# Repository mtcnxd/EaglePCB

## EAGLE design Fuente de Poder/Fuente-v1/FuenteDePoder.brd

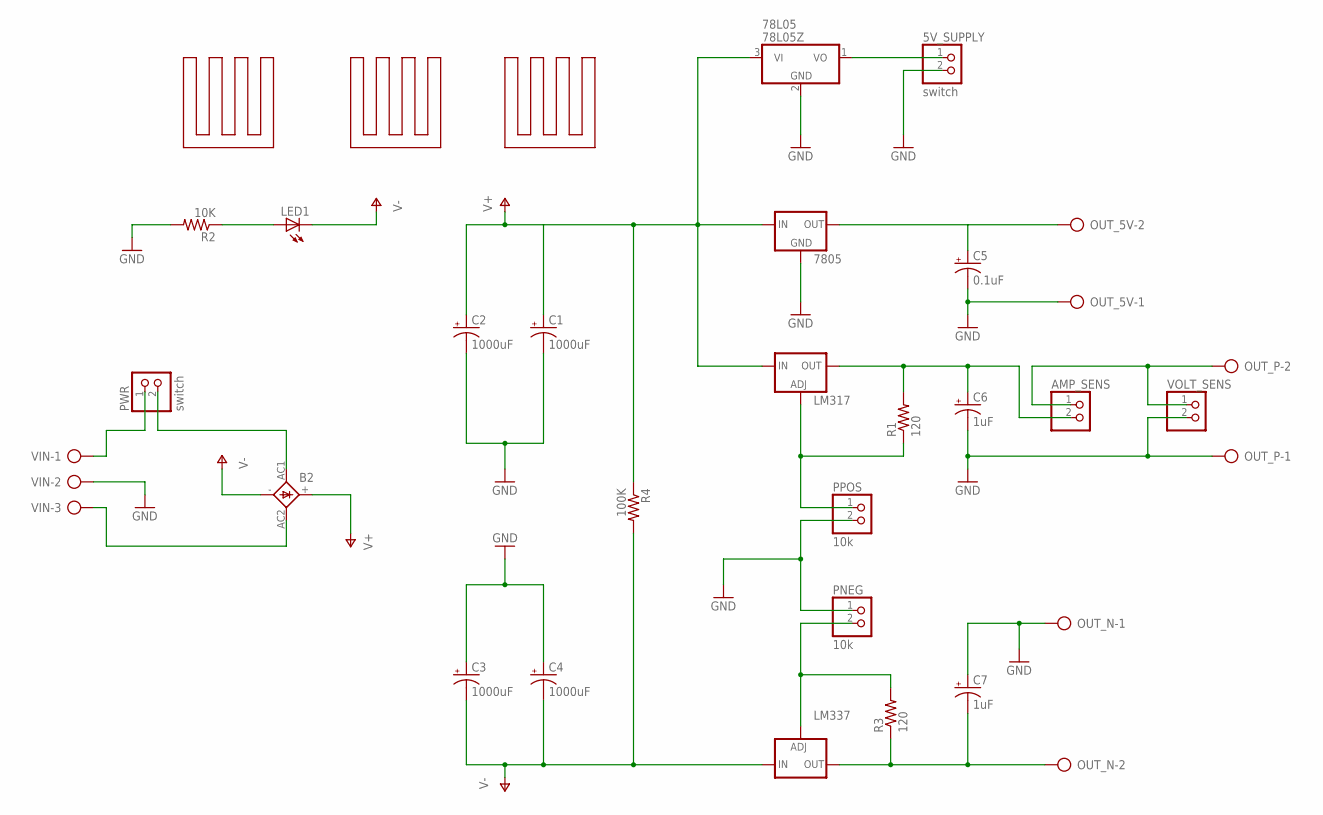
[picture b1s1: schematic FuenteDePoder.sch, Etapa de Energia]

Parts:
5V_SUPPLY: switch; 1X02
78L05: 78L05Z; TO92
7805: 78XXS
AMP_SENS: PINHD-1X2; 1X02
B2: GBPC6
C1, C2, C3, C4: 1000uF; E3,5-10
C5: 0.1uF; E1,8-4
C6, C7: 1uF; E1,8-4
LED1: LED5MM
LM317: LM317TS; 317TS
LM337: LM337TS; 337TS
OUT_5V: AK300/2
OUT_N: AK300/2
OUT_P: AK300/2
PNEG: 10k; 1X02
PPOS: 10k; 1X02
PWR: switch; 1X02
R1, R3: 120; 0204/7
R2: 10K; 0204/7
R4: 100K; 0204/7
U$1, U$2, U$3: HEATSINK
VIN: AK300/3
VOLT_SENS: PINHD-1X2; 1X02

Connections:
GND: 5V_SUPPLY.2, 78L05.2 (GND), 7805.GND, C1.-, C2.-, C3.+, C4.+, C5.-, C6.-, C7.+, OUT_5V.1, OUT_N.1, OUT_P.1, PNEG.1, PPOS.2, R2.2, VIN.2, VOLT_SENS.2
unnamed: B2.AC1, PWR.2
unnamed: B2.AC2, VIN.3
unnamed: LED1.A, R2.1
unnamed: C7.-, LM337.3 (OUT), OUT_N.2, R3.1
unnamed: 5V_SUPPLY.1, 78L05.1 (VO)
unnamed: LM337.1 (ADJ), PNEG.2, R3.2
unnamed: LM317.1 (ADJ), PPOS.1, R1.1
unnamed: PWR.1, VIN.1
unnamed: AMP_SENS.1, OUT_P.2, VOLT_SENS.1
V5: 7805.OUT, C5.+, OUT_5V.2
V12: AMP_SENS.2, C6.+, LM317.2 (OUT), R1.2
V+: 78L05.3 (VI), 7805.IN, B2.+, C1.+, C2.+, LM317.3 (IN), R4.1
V-: B2.-, C3.-, C4.-, LED1.K (C), LM337.2 (IN), R4.2

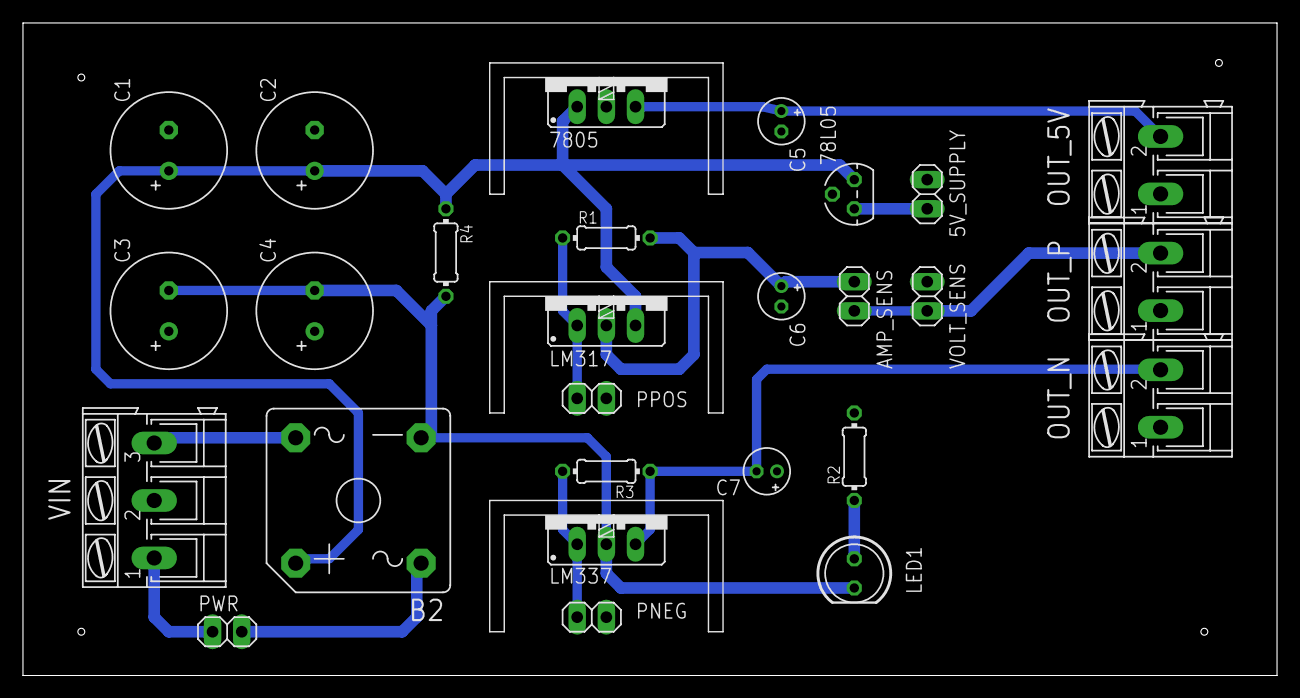
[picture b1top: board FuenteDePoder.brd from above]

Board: 2 copper layers, 109.2 x 56.8 mm, 30 parts (0 on the bottom side), 14 nets.

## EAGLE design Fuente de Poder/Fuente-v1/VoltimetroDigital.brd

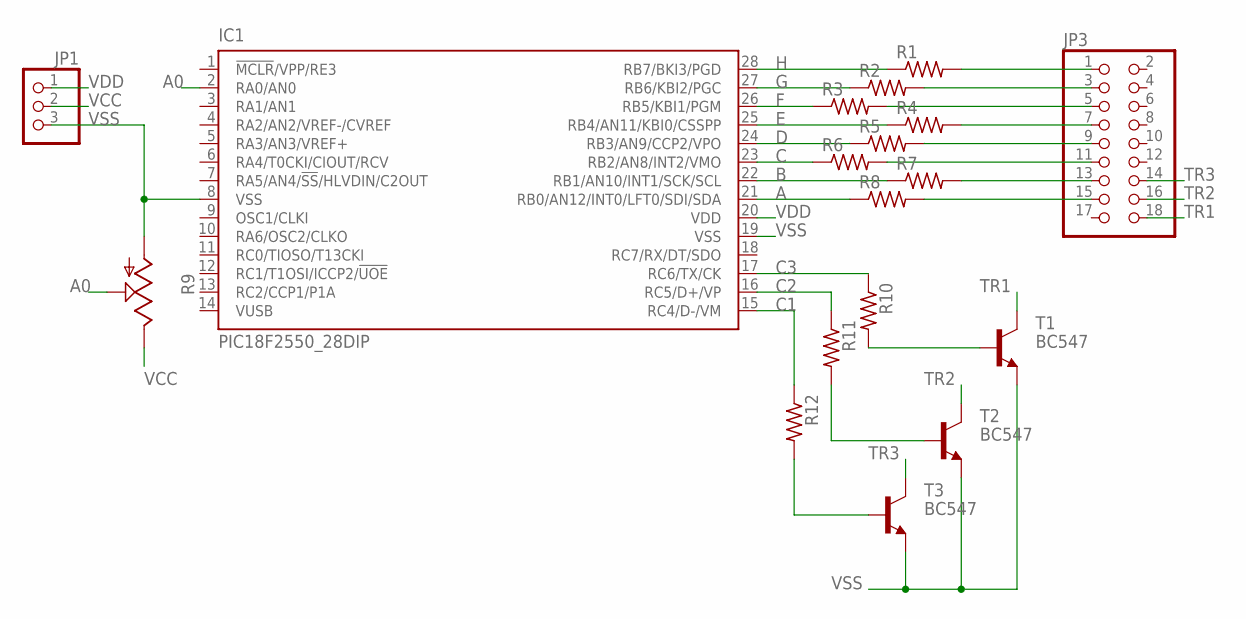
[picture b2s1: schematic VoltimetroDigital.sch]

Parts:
IC1: PIC18F2550_28DIP; DIL28-3
JP1: PINHD-1X3; 1X03
JP3: PINHD-2X9; 2X09
R1, R2, R3, R4, R5, R6, R7, R8, R10, R11, R12: R-US_0204/7; 0204/7
R9: TRIM_US-LI10; LI10
T1, T2, T3: BC547; TO92

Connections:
A: IC1.21 (RB0/AN12/INT0/LFT0/SDI/SDA), R8.1
A0: IC1.2 (RA0/AN0), R9.S
B: IC1.22 (RB1/AN10/INT1/SCK/SCL), R7.1
C: IC1.23 (RB2/AN8/INT2/VMO), R6.1
C1: IC1.15 (RC4/D-/VM), R12.1
C2: IC1.16 (RC5/D+/VP), R11.1
C3: IC1.17 (RC6/TX/CK), R10.1
D: IC1.24 (RB3/AN9/CCP2/VPO), R5.1
E: IC1.25 (RB4/AN11/KBI0/CSSPP), R4.1
F: IC1.26 (RB5/KBI1/PGM), R3.1
G: IC1.27 (RB6/KBI2/PGC), R2.1
H: IC1.28 (RB7/BKI3/PGD), R1.1
unnamed: JP3.1, R1.2
unnamed: JP3.3, R2.2
unnamed: JP3.5, R3.2
unnamed: JP3.7, R4.2
unnamed: JP3.9, R5.2
unnamed: JP3.11, R6.2
unnamed: JP3.13, R7.2
unnamed: JP3.15, R8.2
unnamed: R12.2, T3.2 (B)
unnamed: R11.2, T2.2 (B)
unnamed: R10.2, T1.2 (B)
TR1: JP3.18, T1.3 (C)
TR2: JP3.16, T2.3 (C)
TR3: JP3.14, T3.3 (C)
VCC: JP1.2, R9.E
VDD: IC1.20 (VDD), JP1.1
VSS: IC1.8 (VSS), IC1.19 (VSS), JP1.3, R9.A, T1.1 (E), T2.1 (E), T3.1 (E)

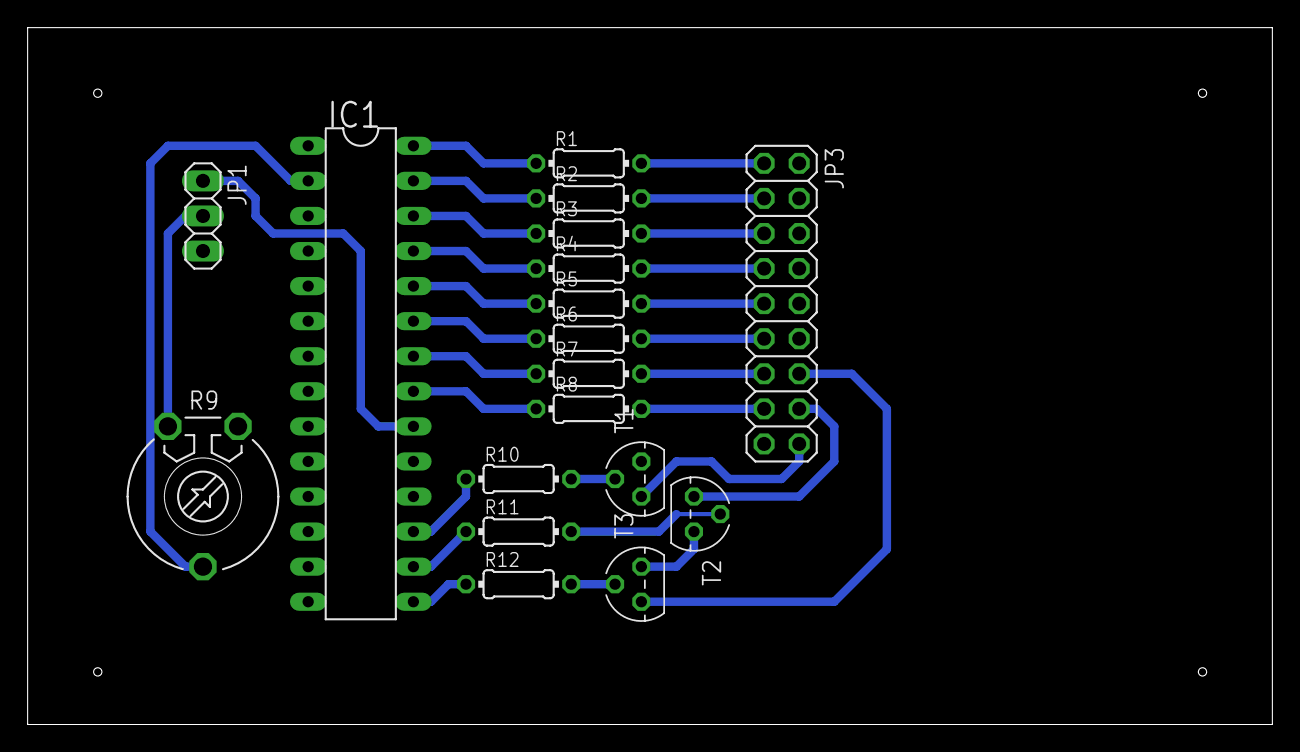
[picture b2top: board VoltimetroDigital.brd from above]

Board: 2 copper layers, 90.2 x 50.5 mm, 18 parts (0 on the bottom side), 29 nets.

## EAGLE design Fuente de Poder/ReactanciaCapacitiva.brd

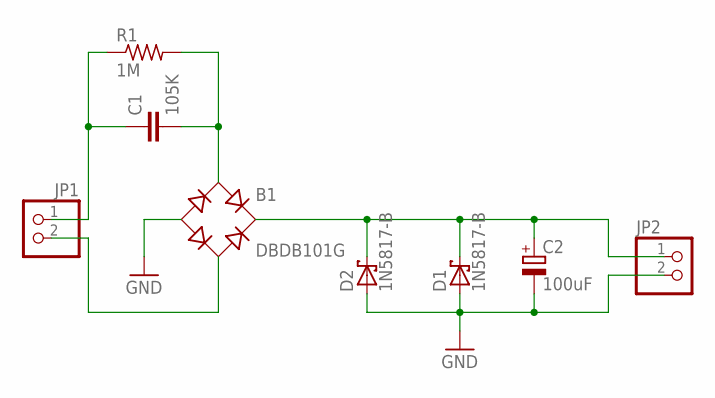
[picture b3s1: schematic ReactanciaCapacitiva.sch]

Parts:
B1: DBDB101G; DB
C1: 105K; C15B7
C2: 100uF; E2,5-7
D1, D2: 1N5817-B; DO41-7.6
JP1: PINHD-1X2/90; 1X02/90
JP2: PINHD-1X2; 1X02
R1: 1M; 0204/7

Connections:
GND: B1.-, C2.-, D1.A, D2.A, JP2.2
unnamed: C1.1, JP1.1, R1.1
unnamed: B1.AC2, JP1.2
unnamed: B1.AC1, C1.2, R1.2
unnamed: B1.+, C2.+, D1.C, D2.C, JP2.1

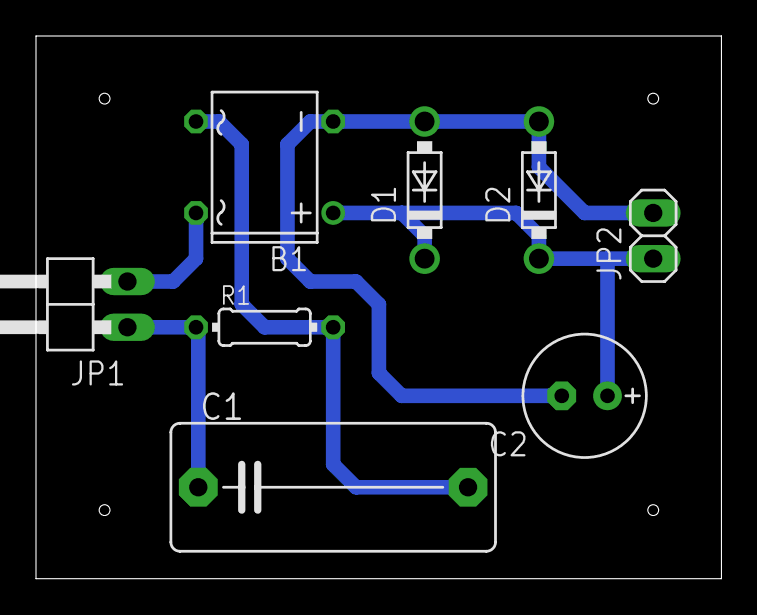
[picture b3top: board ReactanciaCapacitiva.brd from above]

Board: 2 copper layers, 38.1 x 30.1 mm, 8 parts (0 on the bottom side), 5 nets.

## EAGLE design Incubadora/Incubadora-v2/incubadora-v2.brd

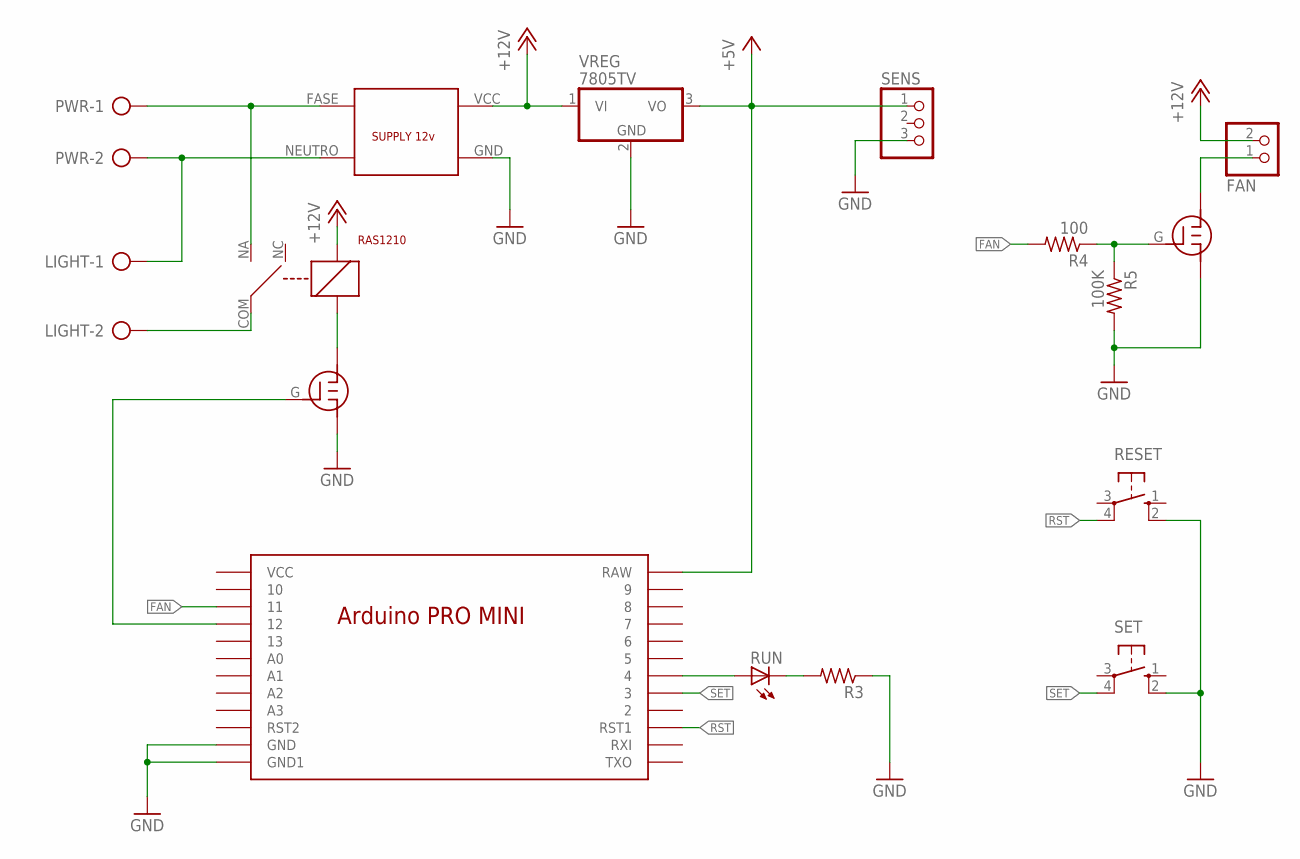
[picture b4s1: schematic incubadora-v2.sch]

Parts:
FAN: PINHD-1X2/90; 1X02/90
LIGHT: AK300/2
PWR: AK300/2
R3: R-US_0204/7; 0204/7
R4: 100; 0204/7
R5: 100K; 0204/7
RAS1210: RAS0510
RESET: 10-XX; B3F-10XX
RUN: LED5MM
SENS: PINHD-1X3/90; 1X03/90
SET: 10-XX; B3F-10XX
U$1: PROMINI
U$2, U$4: J111
U$3: SUPPLY12V
VREG: 7805TV; TO220V

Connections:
+5V: SENS.1, U$1.RAW, VREG.3 (VO)
+12V: FAN.2, RAS1210.B1, U$3.VCC, VREG.1 (VI)
BULB: U$1.12, U$4.G
FAN: R4.2, U$1.11
FASE: PWR.1, RAS1210.NA, U$3.FASE
GND: R3.1, R5.2, RESET.2 (S1), SENS.3, SET.2 (S1), U$1.GND1 (GND), U$1.GND2 (GND1), U$2.S, U$3.GND, U$4.S, VREG.2 (GND)
unnamed: RUN.A, U$1.4
unnamed: LIGHT.2, RAS1210.COM
unnamed: RAS1210.B2, U$4.D
unnamed: R3.2, RUN.K (C)
unnamed: LIGHT.1, PWR.2, U$3.NEUTRO
unnamed: R4.1, R5.1, U$2.G
unnamed: FAN.1, U$2.D
RST: RESET.4 (P1), U$1.RST1
SET: SET.4 (P1), U$1.3

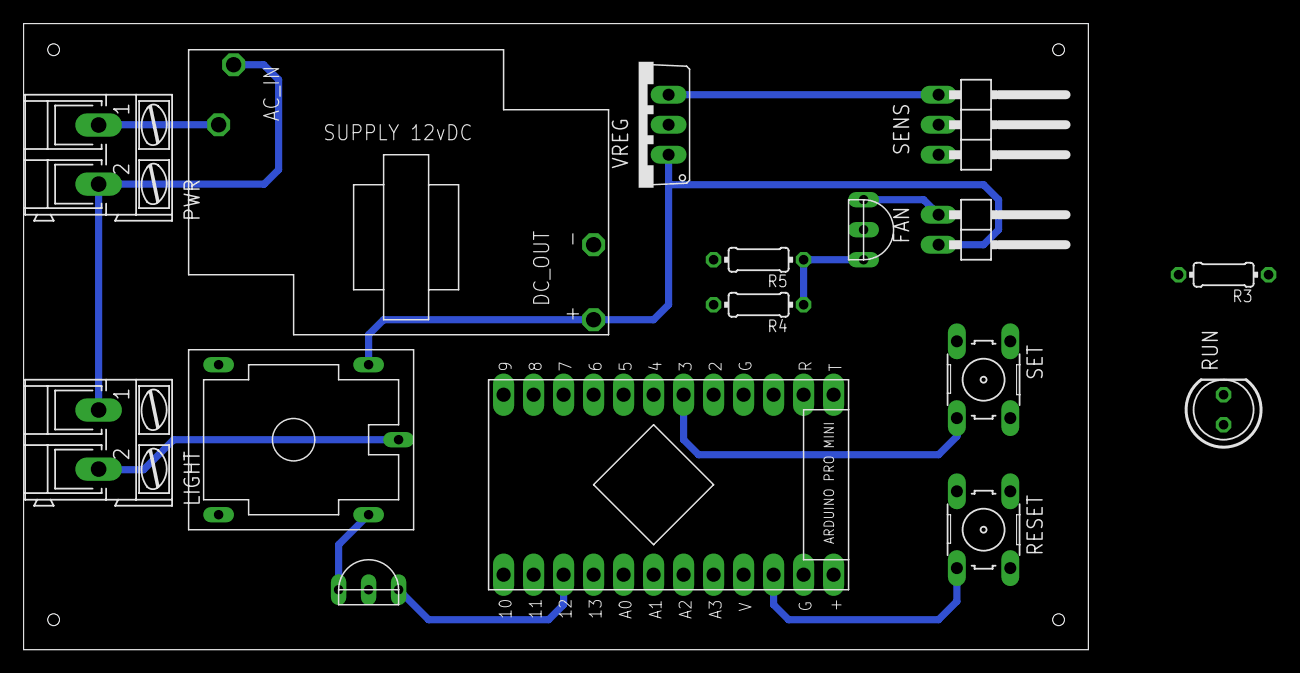
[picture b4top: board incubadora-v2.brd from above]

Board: 2 copper layers, 90.2 x 53.0 mm, 16 parts (0 on the bottom side), 15 nets.

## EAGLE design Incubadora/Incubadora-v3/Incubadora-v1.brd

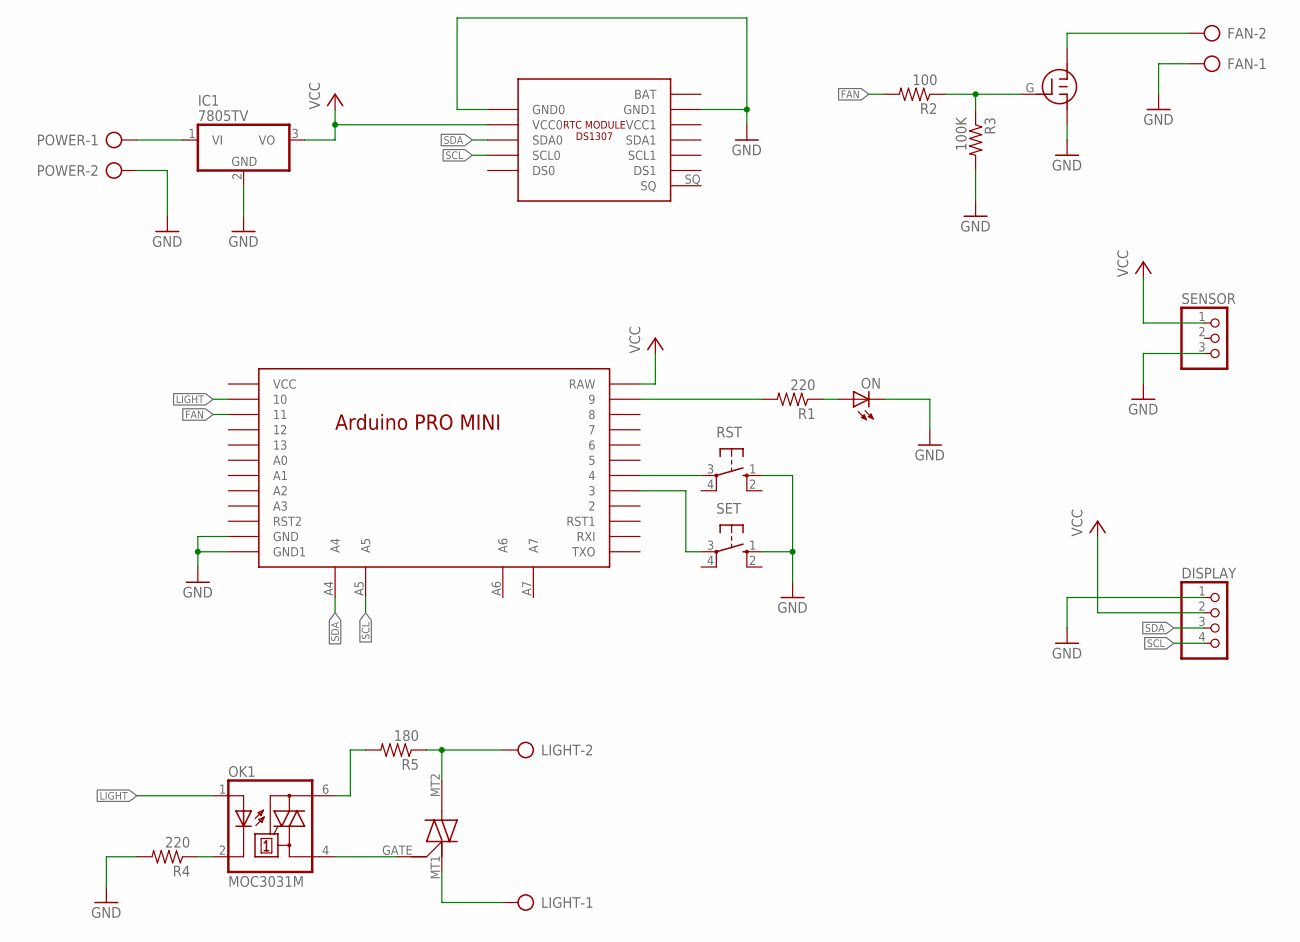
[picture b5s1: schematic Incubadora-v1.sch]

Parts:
DISPLAY: PINHD-1X4; 1X04
FAN: AK300/2
IC1: 7805TV; TO220V
LIGHT: AK300/2
MAC12: MAC12
OK1: MOC3031M; DIL06
ON: LED3MM
POWER: AK300/2
R1, R4: 220; 0204/7
R2: 100; 0204/7
R3: 100K; 0204/7
R5: 180; 0204/7
RST: 10-XX; B3F-10XX
SENSOR: PINHD-1X3/90; 1X03/90
SET: 10-XX; B3F-10XX
U$1: CLOCK
U$2: PROMINI
U$3: J111

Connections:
FAN: R2.2, U$2.11
GND: DISPLAY.1, FAN.1, IC1.2 (GND), ON.K (C), POWER.2, R3.2, R4.2, RST.1 (S), SENSOR.3, SET.1 (S), U$1.GND0, U$1.GND1, U$2.GND1 (GND), U$2.GND2 (GND1), U$3.S
LIGHT: OK1.1 (A), U$2.10
unnamed: ON.A, R1.1
unnamed: IC1.1 (VI), POWER.1
unnamed: RST.3, U$2.4
unnamed: SET.3, U$2.3
unnamed: R1.2, U$2.9
unnamed: FAN.2, U$3.D
unnamed: R2.1, R3.1, U$3.G
unnamed: LIGHT.2, MAC12.MT2, R5.1
unnamed: LIGHT.1, MAC12.MT1
unnamed: OK1.2 (C), R4.1
unnamed: MAC12.GATE, OK1.4 (A1)
unnamed: OK1.6 (A2), R5.2
SCL: DISPLAY.4, U$1.SCL0, U$2.A5
SDA: DISPLAY.3, U$1.SDA0, U$2.A4
VCC: DISPLAY.2, IC1.3 (VO), SENSOR.1, U$1.VCC0, U$2.RAW

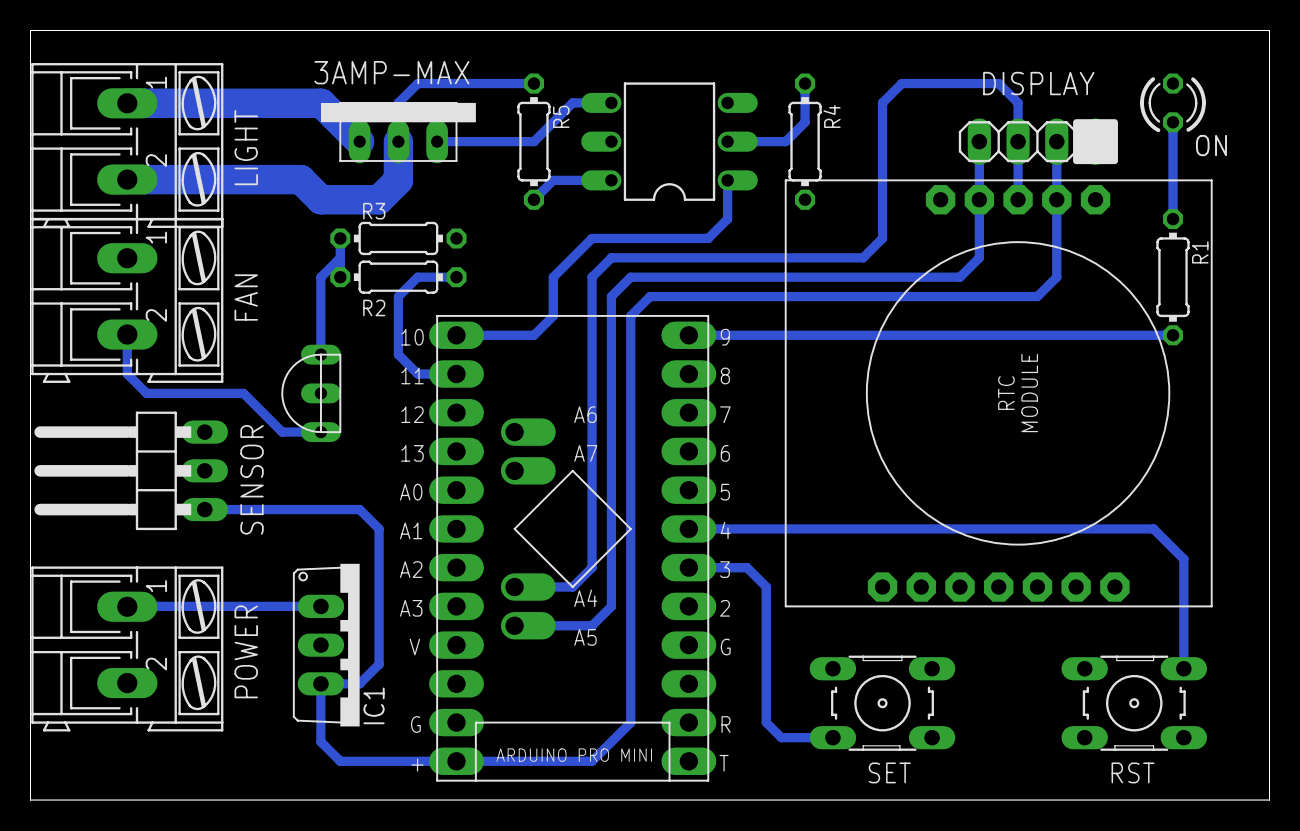
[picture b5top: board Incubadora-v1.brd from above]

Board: 2 copper layers, 81.3 x 50.5 mm, 19 parts (0 on the bottom side), 18 nets.

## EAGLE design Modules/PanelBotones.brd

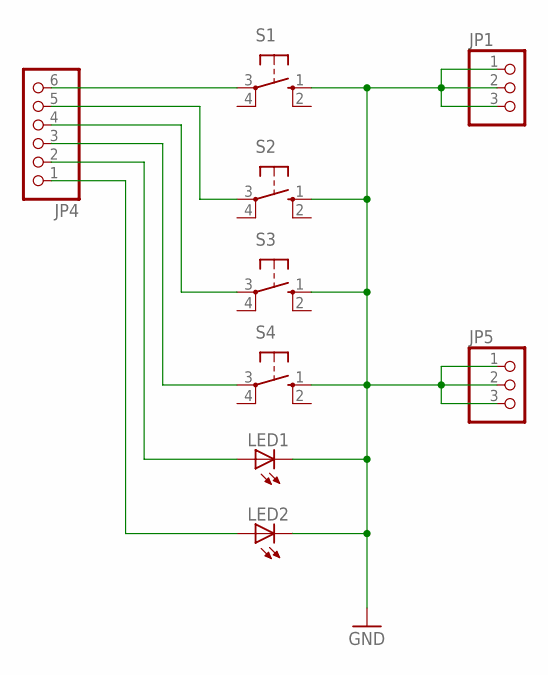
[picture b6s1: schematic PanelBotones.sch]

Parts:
JP1, JP5: PINHD-1X3; 1X03
JP4: PINHD-1X6; 1X06
LED1, LED2: LED3MM
S1, S2, S3, S4: 10-XX; B3F-10XX

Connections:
GND: JP1.1, JP1.2, JP1.3, JP5.1, JP5.2, JP5.3, LED1.K (C), LED2.K (C), S1.1 (S), S2.1 (S), S3.1 (S), S4.1 (S)
unnamed: JP4.6, S1.3
unnamed: JP4.5, S2.3
unnamed: JP4.4, S3.3
unnamed: JP4.3, S4.3
unnamed: JP4.2, LED1.A
unnamed: JP4.1, LED2.A

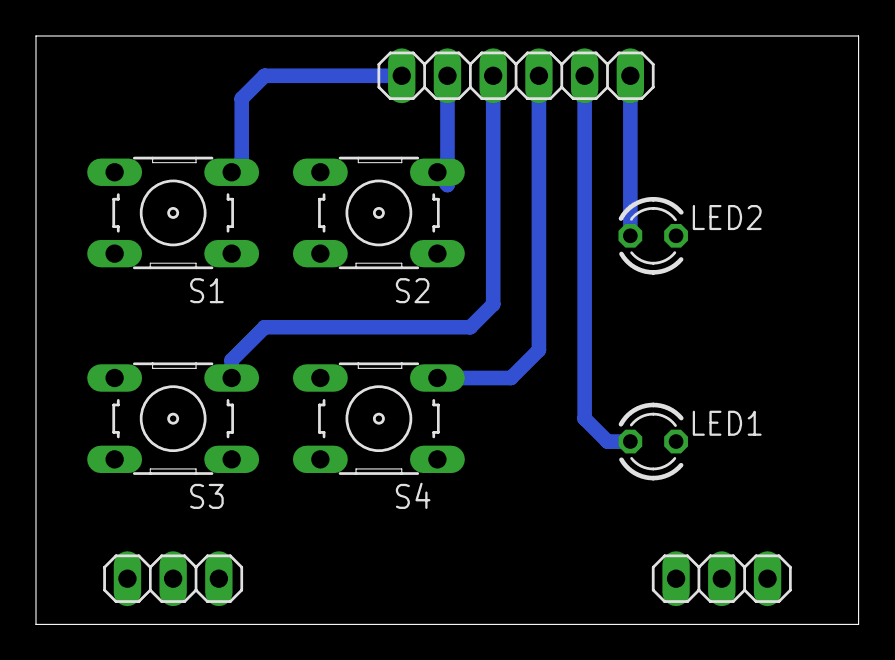
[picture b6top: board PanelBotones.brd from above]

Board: 2 copper layers, 45.7 x 32.7 mm, 9 parts (0 on the bottom side), 7 nets.

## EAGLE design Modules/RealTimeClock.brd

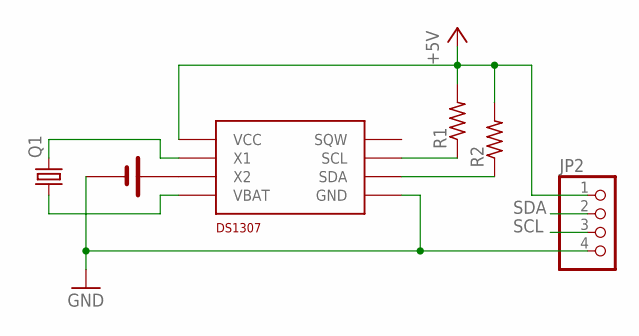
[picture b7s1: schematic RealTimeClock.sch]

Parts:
CR2032: CR2032
JP2: PINHD-1X4/90; 1X04/90
Q1: CRYSTALTC38H; TC38H
R1, R2: R-US_0204/7; 0204/7
U$1: DS1307

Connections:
+5V: JP2.1, R1.2, R2.2, U$1.VCC
GND: CR2032.VCC, JP2.4, U$1.GND
unnamed: CR2032.GND, U$1.X2
unnamed: Q1.2, U$1.X1
unnamed: Q1.1, U$1.VBAT
SCL: JP2.3, R1.1, U$1.SCL
SDA: JP2.2, R2.1, U$1.SDA

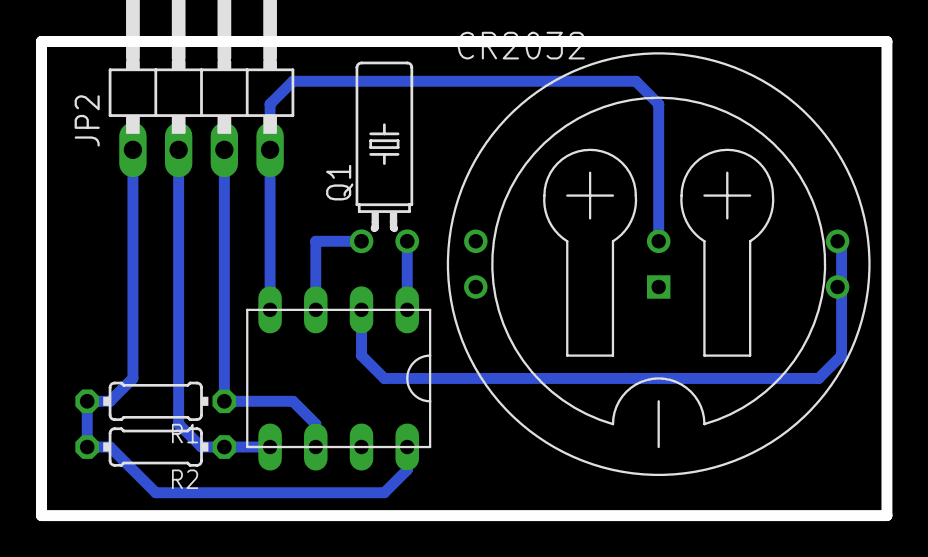
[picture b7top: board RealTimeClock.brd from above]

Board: 2 copper layers, 47.0 x 26.3 mm, 6 parts (0 on the bottom side), 7 nets.

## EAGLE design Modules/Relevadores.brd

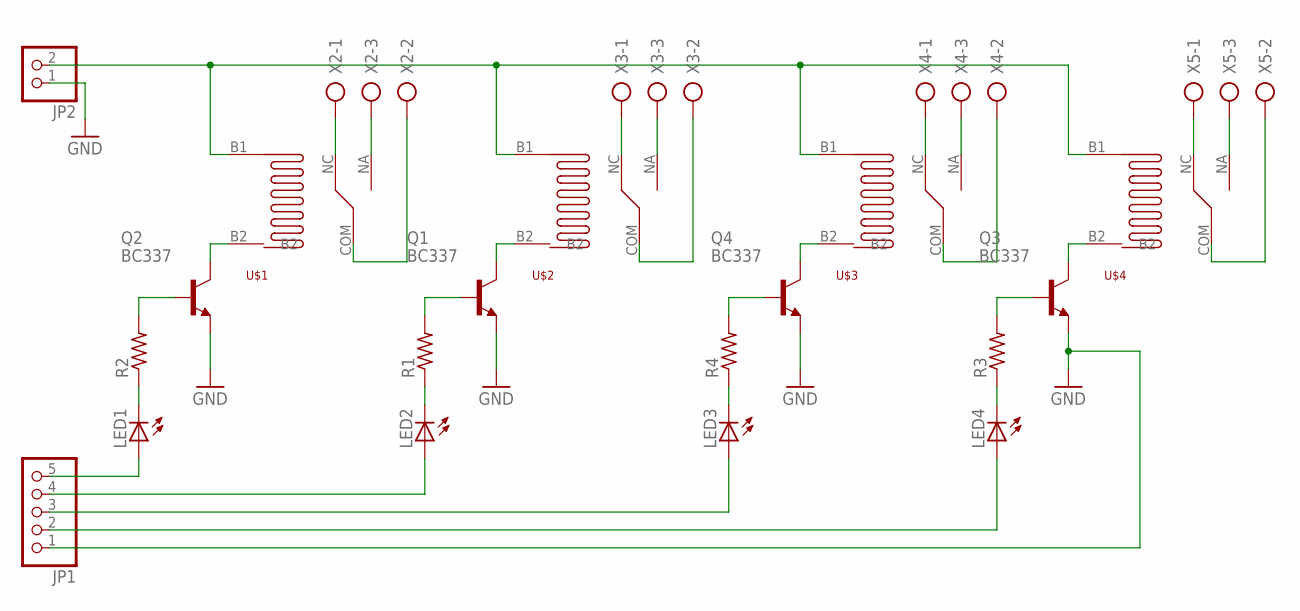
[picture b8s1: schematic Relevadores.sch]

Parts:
JP1: PINHD-1X5/90; 1X05/90
JP2: PINHD-1X2/90; 1X02/90
LED1, LED2, LED3, LED4: LED3MM
Q1, Q2, Q3, Q4: BC337; TO92
R1, R2, R3, R4: R-US_0207/2V; 0207/2V
U$1, U$2, U$3, U$4: RAS-0510
X2, X3, X4, X5: AK300/3

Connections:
GND: JP1.1, JP2.1, Q1.1 (E), Q2.1 (E), Q3.1 (E), Q4.1 (E)
unnamed: Q1.3 (C), U$2.B2
unnamed: Q1.2 (B), R1.2
unnamed: JP2.2, U$1.B1, U$2.B1, U$3.B1, U$4.B1
unnamed: Q4.3 (C), U$3.B2
unnamed: Q4.2 (B), R4.2
unnamed: Q2.3 (C), U$1.B2
unnamed: Q2.2 (B), R2.2
unnamed: Q3.3 (C), U$4.B2
unnamed: Q3.2 (B), R3.2
unnamed: U$1.NC, X2.1
unnamed: U$1.NA, X2.3
unnamed: U$1.COM, X2.2
unnamed: U$2.NC, X3.1
unnamed: U$2.NA, X3.3
unnamed: U$2.COM, X3.2
unnamed: U$3.NC, X4.1
unnamed: U$3.NA, X4.3
unnamed: U$3.COM, X4.2
unnamed: U$4.NC, X5.1
unnamed: U$4.NA, X5.3
unnamed: U$4.COM, X5.2
unnamed: LED2.K (C), R1.1
unnamed: JP1.5, LED1.A
unnamed: JP1.4, LED2.A
unnamed: JP1.3, LED3.A
unnamed: JP1.2, LED4.A
unnamed: LED3.K (C), R4.1
unnamed: LED4.K (C), R3.1
unnamed: LED1.K (C), R2.1

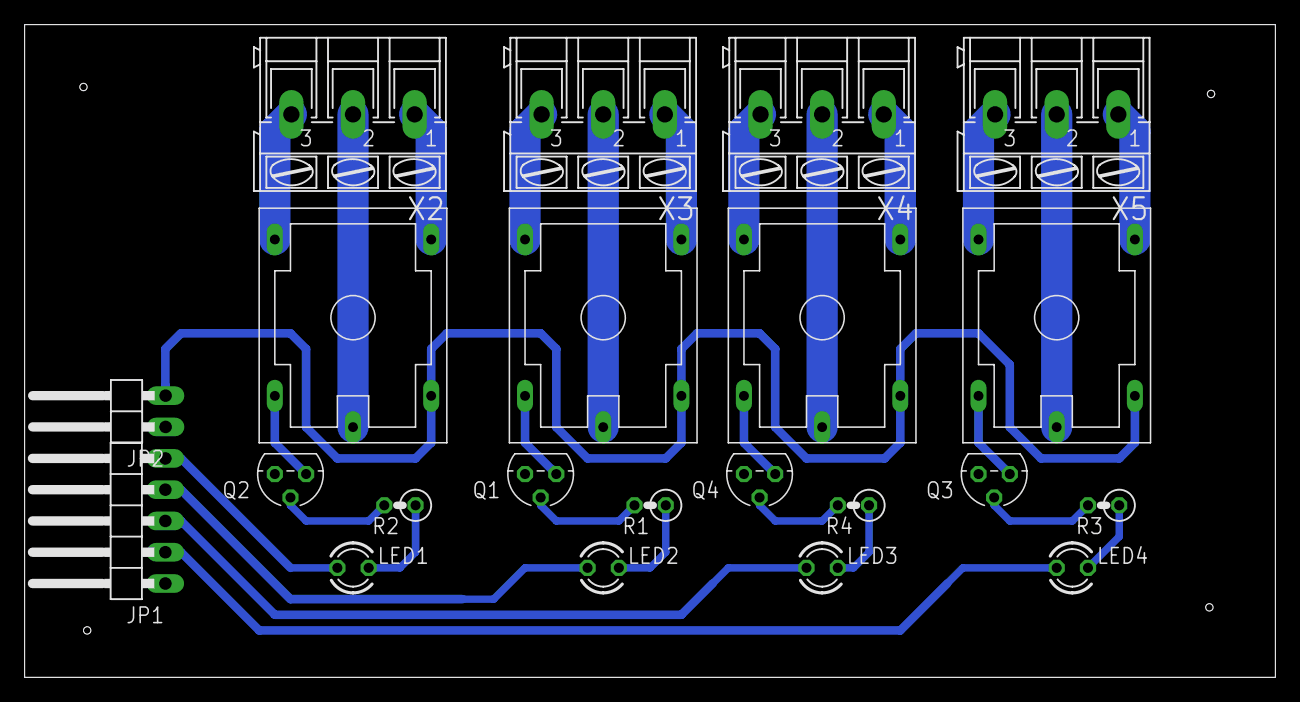
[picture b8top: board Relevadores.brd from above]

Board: 2 copper layers, 101.6 x 53.0 mm, 22 parts (0 on the bottom side), 30 nets.
